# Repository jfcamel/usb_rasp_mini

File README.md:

# usb_rasp_mini
Mini USB serial shield for Raspberry PI

Gerber: [rasp_usb.zip](gerber/rasp_usb.zip)

BOM: [bom.csv](assemble/rasp_usb.csv)

CPL: [The CPL](assemble/rasp_usb-all-pos.csv)

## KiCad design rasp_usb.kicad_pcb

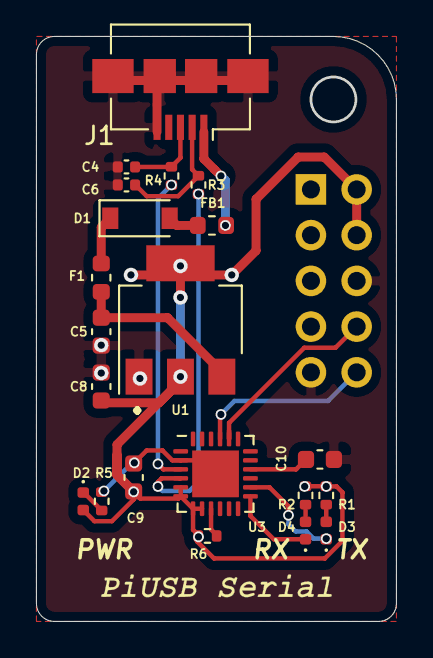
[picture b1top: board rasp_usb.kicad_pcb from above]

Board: 2 copper layers, 19.9 x 32.4 mm, 22 parts (1 on the bottom side), 19 nets.

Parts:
C4, C6: 47p; C_0402_1005Metric
C5, C8: 100n; C_0603_1608Metric
C9: 1u; C_0603_1608Metric
C10: 4.7u; C_0603_1608Metric
D1: D_Small; D_SOD-123
D2: LED_PWR; LED_0402_1005Metric
D3: LED_TX; LED_0402_1005Metric
D4: LED_RX; LED_0402_1005Metric
F1: 500mA; Fuse_0603_1608Metric
FB1: Ferrite_Bead_Small; L_0603_1608Metric
J1: USB_B_Micro; USB_Micro-B_Amphenol_10104110_Horizontal
J2: Conn_02x05_Odd_Even; PinSocket_2x05_P2.54mm_Vertical
R1, R2, R5: 2.2k; R_0402_1005Metric
R3, R4: 27; R_0402_1005Metric
R6: 4.7k; R_0402_1005Metric
U1: AMS1117-5.0; SOT-223-3_TabPin2
U3: CP2104; QFN-24-1EP_4x4mm_P0.5mm_EP2.6x2.6mm

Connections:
+5V: C8.1, C9.1, D2.2, J2.2, J2.4, R1.1, R2.2, R6.1, U1.2, U3.5, U3.6, U3.7, U3.8
GND: C4.2, C5.2, C6.2, C8.2, C9.2, C10.2, J1.5, J1.6, J2.6, J2.9, R5.2, U1.1, U3.2, U3.25
unnamed: C5.1, F1.2, U1.3
unnamed: C10.1, U3.16
unnamed: D1.1, F1.1
unnamed: D1.2, FB1.1
unnamed: D2.1, R5.1
unnamed: D3.1, U3.14
unnamed: D3.2, R1.2
unnamed: D4.1, U3.13
unnamed: D4.2, R2.1
unnamed: R3.2, U3.4
unnamed: R4.2, U3.3
unnamed: R6.2, U3.9
UART_RXD: J2.10, U3.21
UART_TXD: J2.8, U3.20
USB_DM: C6.1, J1.2, R3.1
USB_DP: C4.1, J1.3, R4.1
VBUS: FB1.2, J1.1

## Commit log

2020-11-25 ftdi ic is out of stock
2020-11-25 ready to order
2020-11-25 Replaced usb IC with cp2104. Ready to order
2020-11-25 Modify sch
2020-11-25 cp210x
2020-12-14 thin board
2021-01-10 Updated schematics as hierarchical structure
2021-01-10 Updated png
2021-01-10 annotation number
2021-01-14 Update README.md
    Added Links in README.md
